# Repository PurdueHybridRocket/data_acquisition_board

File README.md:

# data_acquisition_board
Software and hardware associated with the hybrid rocket data acquisition board. Developed by Purdue Space Program's Hybrid Rocket for the HAVOC vehicle. 

Hardware:
The data acquisition board is built on a TEENSY 3.6 microcontroller which reads data from the following sensors:
BMP 280 temperature and pressure sensor
MPU 9250 9-axis inertial measurement unit (IMU)
GNSS Module
Tactile switch

And outputs the data to the following media:
microSD card
SSD1306 LCD Display

Software:
The software for the board is written in Arduino using the Arduino IDE and the Teensyduino plugin. The code running on the board makes use of the following libraries:
MPU9250.h             from https://github.com/hideakitai/MPU9250
Adafruit_BMP280.h     from https://github.com/adafruit/Adafruit_BMP280_Library
TinyGPS++.h           from https://github.com/mikalhart/TinyGPSPlus
SoftwareSerial.h      from https://www.arduino.cc/en/Reference/SoftwareSerial
SD.h                  from https://www.arduino.cc/en/Reference/SD
Adafruit_GFX.h        from https://github.com/adafruit/Adafruit-GFX-Library
Adafruit_SSD1306.h    from https://github.com/adafruit/Adafruit_SSD1306
BasicLinearAlgebra.h  from https://github.com/tomstewart89/BasicLinearAlgebra
Fonts/Picopixel.h     from https://github.com/adafruit/Adafruit-GFX-Library

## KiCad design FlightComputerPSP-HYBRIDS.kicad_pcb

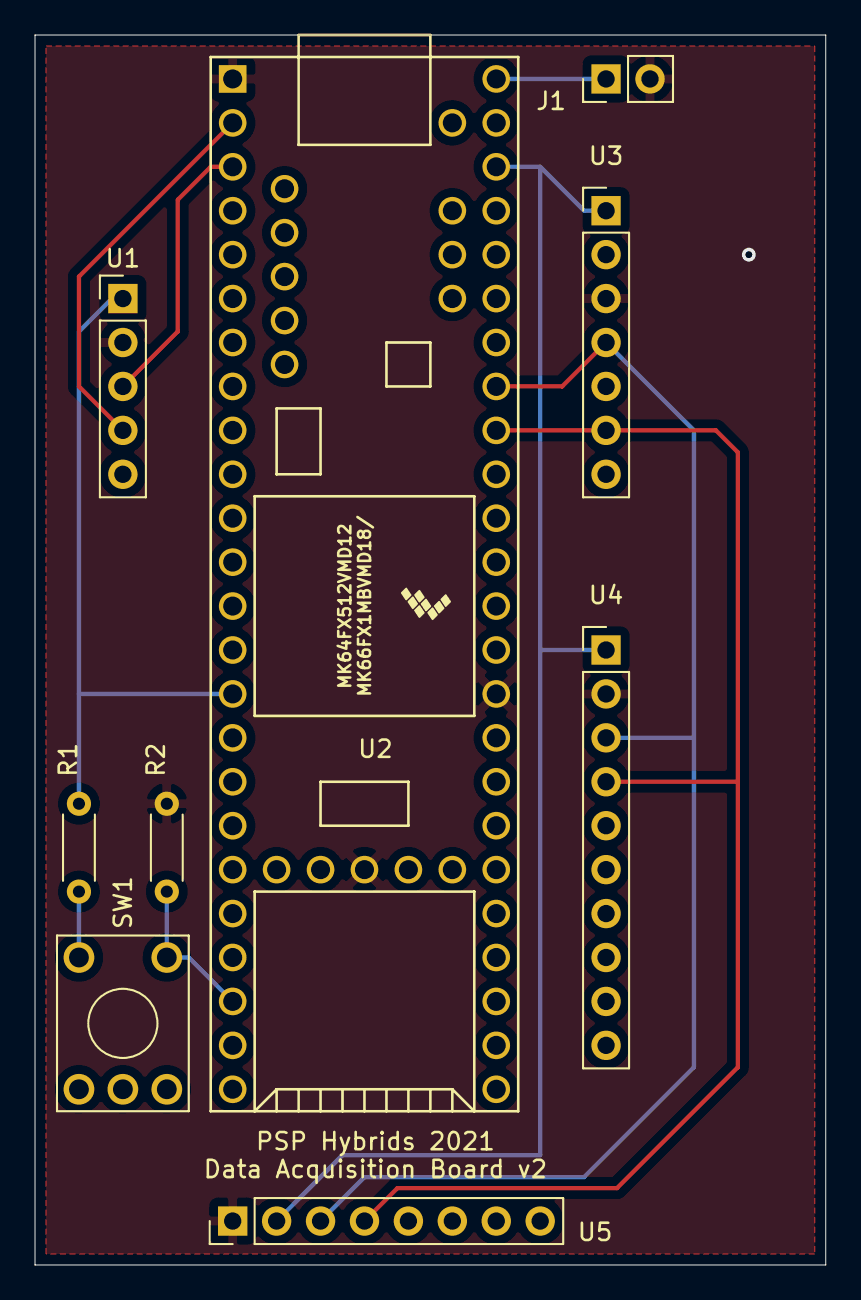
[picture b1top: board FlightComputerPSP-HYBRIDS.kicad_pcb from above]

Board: 2 copper layers, 45.7 x 71.1 mm, 9 parts (0 on the bottom side), 10 nets.

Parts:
J1: Conn_01x02; PinHeader_1x02_P2.54mm_Vertical
R1, R2: R_US; R_Axial_DIN0204_L3.6mm_D1.6mm_P5.08mm_Horizontal
SW1: SW_Push; KSA_Tactile_SPST
U1: NEO6MGPS; PinHeader_1x05_P2.54mm_Vertical
U2: Teensy3.6; Teensy35_36
U3: BMP280; PinHeader_1x07_P2.54mm_Vertical
U4: MPU9250; PinHeader_1x10_P2.54mm_Vertical
U5: SSD1306OLED; PinHeader_1x08_P2.54mm_Vertical

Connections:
GNDREF: J1.2, R2.2, U1.2, U2.1, U2.27, U2.39, U3.3, U4.2, U5.1
unnamed: J1.1, U2.53
unnamed: R1.1, U1.1, U2.15
unnamed: R1.2, SW1.1
unnamed: R2.1, SW1.2, U2.22
unnamed: U1.3, U2.3
unnamed: U1.4, U2.2
unnamed: U2.45, U3.6, U4.4, U5.4
unnamed: U2.46, U3.4, U4.3, U5.3
unnamed: U2.51, U3.1, U4.1, U5.2

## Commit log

2022-02-28 Create description
2022-02-28 Rename FlightComputerPSP-HYBRIDS.kicad_pcb to hardware/FlightComputerPSP-HYBRIDS.kicad_pcb
2022-02-28 Rename hybrids_data_acquisition_PCB.ino to Software/hybrids_data_acquisition_PCB.ino
2022-02-28 Rename hybrids_data_acquisition_PCB_polished.ino to Software/hybrids_data_acquisition_PCB_polished.ino
2022-02-28 Rename FlightComputerPSP-HYBRIDS.kicad_pcb-bak to Hardware/FlightComputerPSP-HYBRIDS.kicad_pcb-bak
2022-02-28 Rename FlightComputerPSP-HYBRIDS.pro to Hardware/FlightComputerPSP-HYBRIDS.pro
2022-02-28 Rename FlightComputerPSP-HYBRIDS.sch to Hardware/FlightComputerPSP-HYBRIDS.sch
